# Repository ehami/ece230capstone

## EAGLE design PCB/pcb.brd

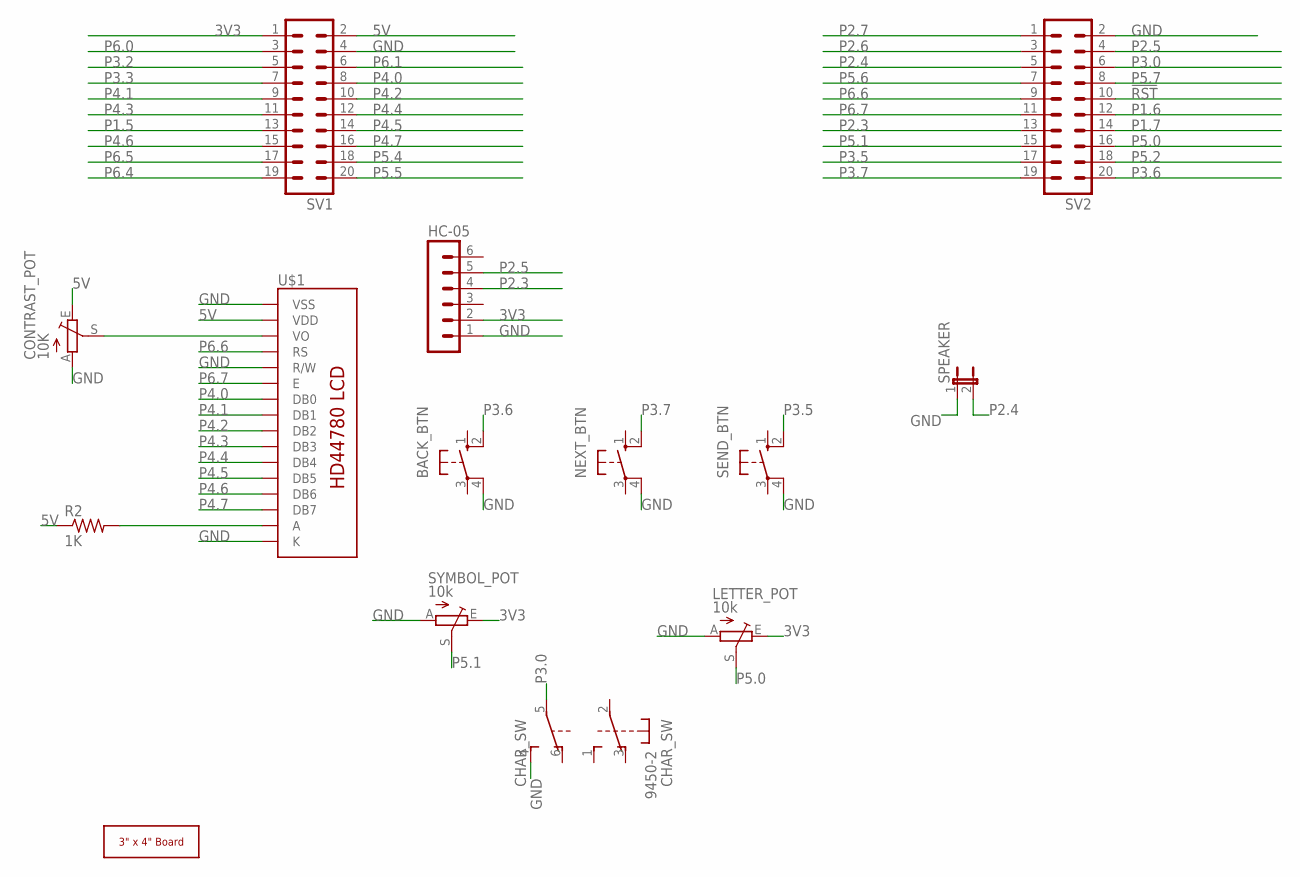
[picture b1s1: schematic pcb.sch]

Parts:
BACK_BTN: 10-XX; B3F-10XX
CHAR_SW: 9450-2
CONTRAST_POT: 10K; B25V
HC-05: MA06-1
LETTER_POT: 10k; B25V
NEXT_BTN: 10-XX; B3F-10XX
R2: 1K; 0204/7
SEND_BTN: 10-XX; B3F-10XX
SPEAKER: JP1E; JP1
SV1, SV2: MA10-2
SYMBOL_POT: 10k; B25V
U$1: LCD-HD447804-HOLES16X2-4-HOLES; LCD-16X2-4HOLES
U$3: 3X4_BOARD; 3X4_BOARD_V1

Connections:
3V3: HC-05.2, LETTER_POT.E, SV1.1, SYMBOL_POT.E
5V: CONTRAST_POT.E, R2.1, SV1.2, U$1.2 (VDD)
!RST: SV2.10
GND: BACK_BTN.4 (P1), CHAR_SW.4 (S), CONTRAST_POT.A, HC-05.1, LETTER_POT.A, NEXT_BTN.4 (P1), SEND_BTN.4 (P1), SPEAKER.1, SV1.4, SV2.2, SYMBOL_POT.A, U$1.1 (VSS), U$1.5 (R/W), U$1.16 (K)
unnamed: CONTRAST_POT.S, U$1.3 (VO)
unnamed: R2.2, U$1.15 (A)
P1.5: SV1.13
P1.6: SV2.12
P1.7: SV2.14
P2.3: HC-05.4, SV2.13
P2.4: SPEAKER.2, SV2.5
P2.5: HC-05.5, SV2.4
P2.6: SV2.3
P2.7: SV2.1
P3.0: CHAR_SW.5, SV2.6
P3.2: SV1.5
P3.3: SV1.7
P3.5: SEND_BTN.2 (S1), SV2.17
P3.6: BACK_BTN.2 (S1), SV2.20
P3.7: NEXT_BTN.2 (S1), SV2.19
P4.0: SV1.8, U$1.7 (DB0)
P4.1: SV1.9, U$1.8 (DB1)
P4.2: SV1.10, U$1.9 (DB2)
P4.3: SV1.11, U$1.10 (DB3)
P4.4: SV1.12, U$1.11 (DB4)
P4.5: SV1.14, U$1.12 (DB5)
P4.6: SV1.15, U$1.13 (DB6)
P4.7: SV1.16, U$1.14 (DB7)
P5.0: LETTER_POT.S, SV2.16
P5.1: SV2.15, SYMBOL_POT.S
P5.2: SV2.18
P5.4: SV1.18
P5.5: SV1.20
P5.6: SV2.7
P5.7: SV2.8
P6.0: SV1.3
P6.1: SV1.6
P6.4: SV1.19
P6.5: SV1.17
P6.6: SV2.9, U$1.4 (RS)
P6.7: SV2.11, U$1.6 (E)

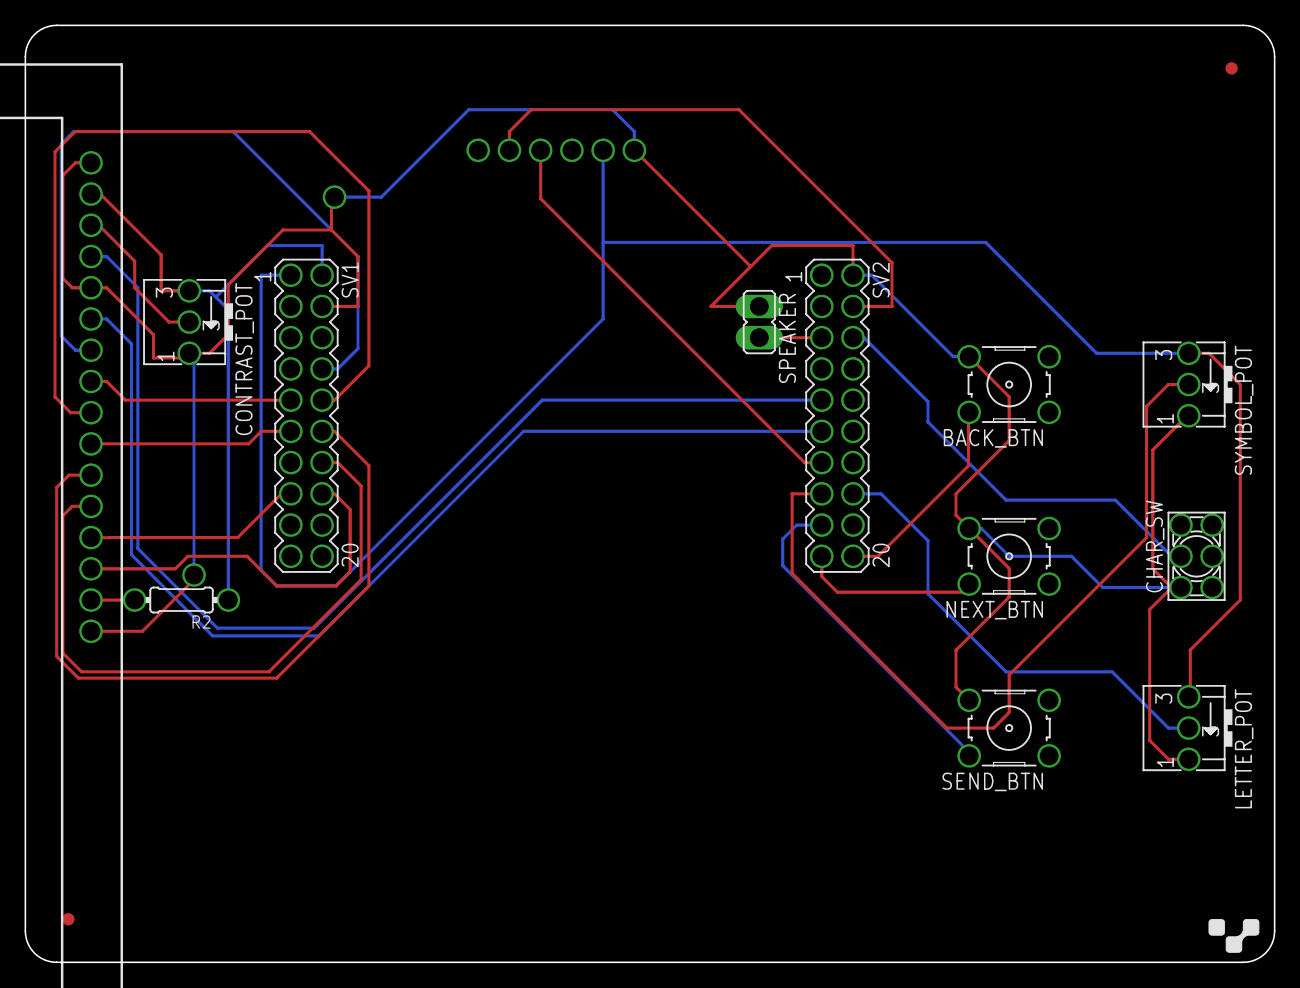
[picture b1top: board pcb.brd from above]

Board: 2 copper layers, 101.6 x 76.2 mm, 14 parts (1 on the bottom side), 24 nets.

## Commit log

2021-05-21 Message Send/Recieve notification
2021-05-23 Notification sound is interrupt based, cleaned up and commented code.
2021-05-23 Removed unnecessary files
2021-05-24 Add PCB files
2021-05-24 Cleanup serial code
